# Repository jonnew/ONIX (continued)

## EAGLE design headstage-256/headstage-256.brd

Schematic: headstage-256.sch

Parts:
3V1: TPTP10R; TP10R
C1, C2: 0.1uF; 0201T; PARTNP CL03A104KA3NNNC
C3, C13, C14, C18, C19, C32, C51: 10nF; 0201T
C4, C12, C15, C17, C20, C43, C45, C47, C52, C57, C62, C63, C85, C89, C92, C93, C95, C100: 0.1uF; 0201T
C5, C16: 4.7uF; 0402T; PARTNO GRM155R61A475MEAAD
C6, C7, C8, C9, C24, C41, C42, C48, C60, C66, C71, C75, C79, C98: 0.1uF; 0201T; PARTNO C0603X5R1C104K030BC
C10, C11, C22, C23, C26, C27, C44: 0.1uF; 0201T; PARTNO CL03A104KA3NNNC
C21: 22uF; 0603T; PARTNO CL05A226MQ5QUNC
C25: 4.7uF; 0402T; PARTNO CL05A475MO5NUNC
C28: 0.1uF; 0201T; PARTNO C1005X7R1H104K050BB
C29: 47nF; 0201T; PARTNO C1005X7R1H473K050BB
C30: 1.5pF, NP0 +/-0.1pF; 0402T
C31: 1.0pF, NP0 +/- 0.1pF; 0402T
C33: 1nF; 0201T
C34: 33nF; 0201T
C35: 2.2nF; 0402T
C36: 4.7pF, NP0 +/-0.25pF; 0402T
C37, C40, C64, C69, C73: 1uF; 0402T; PARTNO CL05A105KO5NNNC
C38, C39, C49, C50: 22pF, NP0 2%; 0402T
C46: 6.8nF; 0201T; PARTNO CL03B103KP3NNNC
C53, C54, C77, C78, C86, C90, C96, C101: 4.7uF; 0402T
C55, C56: 22uF; 0603T
C58, C59, C80, C81: 10nF; 0201T; PARTNO GRM033R71E103KE14D
C61, C67, C72, C76, C82, C103: 1uF; 0201T; PARTNO CL03A105MP3ZSNH
C65, C70: 0.47uF; 0402T; PARTNO UMK105BJ224KV-F
C68: 10pF; 0201T
C74: 10uF; 0402T; PARTNO CL05A106MQ5NUNC
C83, C84, C88, C94, C99: 22nF; 0201T
C87, C91, C97, C102: 10uF; 0402T
D1: SESD0402X1UN-0020-090; 0402T-DFN
D2: SESD0402X1UN-0020-090; 0402P-DFN
D3: GDZ8V2BLP3-7; GDZ8V2BLP3
D4, D5, D9, D10, D11: VEMD1160X01; 0805PT
D6, D7: XZVGR155W; LED-0201T
D8: VSKY05401006; CLP1006-2L
GND: TPTP10R; TP10R
J1, J2: JP2E_COAX-ADAPTER-8X8MM-SIG-THRU; COAX-ADAPTER-8X8MM-SIG-THRU
J3: 142-0711-201; SMA_VERT
J4, J6: COAX_COAX-ADAPTER-8X8MM-THRU; COAX-ADAPTER-8X8MM-THRU
J5: MMCX-J-P-H-ST-SM1; MMCX-SMT-VERT
J7, J8: JP2E_COAX-ADAPTER-8X8MM-GND-THRU; COAX-ADAPTER-8X8MM-GND-THRU
J9: COAX_COAX-ADAPTER-8X8MM-SMD; COAX-ADAPTER-8X8MM
J10: X_FL_R_SMT_1(02)
J11: PINHD-2X10+4_DF40-HEAD; DF40-20HEAD
J12: PINHD-2X5+4DF40-HEAD; DF40-10HEAD
J13: 5041940270; MICROLOCK-1X2-VERT
JA: DF40C(2.0)-70DS-0.4V(51); DF40-70REC
JB: DF40C(2.0)-70DS-0.4V(51); DF40-70REC
JC: DF40C(2.0)-70DS-0.4V(51); DF40-70REC
JD: DF40C(2.0)-70DS-0.4V(51); DF40-70REC
L1, L2, L7, L13, L15, L18, L19: BLM15PX601SN1D; 0402T; PARTNO BLM15PX601SN1D
L3: BLM18KG601SN1D; 0603T
L4: CIG21L4R7MNE; 0805T
L5: CBC3225T101MR; 1210T
L6: 3.9nH, 5%; 0402T
L8: 8.2nH, 5%; 0402T
L9: 2.7nH, 5%; 0402T
L10: MMZ0603S601HT000; 0201T
L11: TFM201610ALM-2R2MTAA, 2.2 uH; 0806T
L12, L14: MLZ2012M100WT000; 0805T
L16: TFM201610ALMA1R5MTAA, 1.5uH; 0806T
L17: BLM15PX121SN1D; 0402T; PARTNO BLM15PX601SN1D
R1, R2, R48: 9k, 0.1%; 0201T
R3, R4, R51: 1k, 0.1%; 0201T
R5, R6, R7, R8, R9, R10, R11, R12, R13, R14, R19, R20, R21, R22, R23, R24, R25, R26, R27, R28, R29, R30: 10k, 0.1%; 0201T
R15, R17, R62, R65, R66, R69, R71, R73, R79, R95, R96, R97: 100; 0201T
R16, R18: 2.86k; 0201T
R31, R32, R58, R59: 1k; 0201T
R33: 49.9; 0201T
R34, R35, R46, R47: 590; 0201T
R36, R37, R38, R39, R40, R42, R45, R52, R53, R54, R55, R57, R82, R87, R88, R89, R91: 10k; 0201T
R41: 100k; 0201T
R43, R74, R85: 1M; 0201T
R44: 22K; 0201T
R49, R75: 0; 0201T
R50, R56, R76, R77: 4.7k; 0201T
R60, R61: 2M; 0201T
R63: 240k; 0201T
R64: 200k; 0201T
R67, R68, R93, R94: 0; 0402
R70, R80, R86, R90, R92, R98: 15k; 0201T
R72: 0 (DNP); 0201T
R78: 90.9k; 0201T
R81: 83.3k; 0201T
R83, R84: 2k; 0201T
TCK: TPTP10R; TP10R
TDI: TPTP10R; TP10R
TDO: TPTP10R; TP10R
TMS: TPTP10R; TP10R
TP1, TP2, TP3, TP4, TP5, TP6, TP7, TP8, TP9, TP10, TP12, TP27, TP33, TP35, TP36: TP_0.7MM; TESTPOINT_0.7MM
TP11, TP13, TP14, TP15: TPTP07R; TP07R
TP16, TP17, TP18, TP19, TP20, TP21, TP22, TP23, TP24, TP25, TP26, TP28, TP29, TP30, TP31, TP32, TP34: TPTP13R; TP13R
U1, U2: ADA4062-4ACPZ-R7; CP_16_27-L
U3, U4: AD5681RBCPZ-1RL7; CP_8_10-L
U5, U6: DG509B; MQFN16-1.8X2.6
U7: DS90UB913A_WQFN; WQFN32-5X5
U8: NRF24L01QFN; QFN20-4X4MM_NO-PAD
U9, U10: CAT4016_QFN; QFN24-4X4; PARTNO CAT4016HV6-GT2
U11, U12: TPL0501_UQFN; UQFN; PARTNO TPL0501-100RSER
U13: MICROSD_473093751; MICRO-SD-473093751
U14: 10M08SAM15317G; MBGA153-8X8
U15: Si8487DB; MICROFOOT-1.6X1.6MM
U16: MAX17048_WLP; WLP8-1.7X0.9
U17: BNO055; LGA-28-3.8X5.2
U18: ASCO-50.000MHZ-EK-T3; ASCO
U19: TPS61202; PWSON-N10+4-3X3
U20, U21, U28, U29: RHD2064_BGA; BGA104_0.5MM
U22, U23, U25, U27, U31, U32: TS4231; WLCSP3X3
U24: LT3463; DFN103X3
U26: TLV70733; X2SON
U30: MIC23150; TDFN_2X2MM
U33: TPS8268180; MICROSIP9-3X2.3
VCOAX: TPTP10R; TP10R
Y1: FW1600008; FW2X1.6MM
Y2: ECS-.327-12.5-1210-TR; ECX-1210

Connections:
!IMU_BL: R55.2, TP11.TP, U17.4 (!BOOT_LOAD)
!IMU_RESET: R57.1, U14.P4 (DIFFIO_RX_B4N/P4), U17.11 (!RESET)
!LIPO_ALRT: R50.1, U14.E7 (DIFFIO_RX_T22N/CRC_ERROR/E7), U16.B4 (!ALRT)
+1V8: C12.1, C13.1, C14.1, C15.1, C16.1, L1.1, L2.1, R38.1, U7.11 (VDDT), U7.28 (VDDD), U33.A1 (VOUT), U33.A2 (VOUT)
+3V3: 3V1.TP, C7.1, C9.1, C17.1, C18.1, C41.1, C42.1, C43.1, C45.1, C46.1, C47.1, C51.1, C60.1, C66.1, C71.1, C75.1, C77.1, C79.1, C98.1, C99.1, C100.1, C101.1, C102.1, J11.17, J11.18, J12.7, J12.8, L7.2, L16.1, L17.1, L18.1, L19.1, R36.1, R37.1, R42.1, R45.2, R50.2, R52.1, R53.1, R54.1, R55.1, R57.2, R72.2, R76.2, R77.2, R83.1, R84.1, R87.1, R88.1, R89.1, TP6.1, U3.2 (VLOGIC), U4.2 (VLOGIC), U7.25 (VDDIO), U11.7 (VDD), U12.7 (VDD), U13.VDD (VCC), U14.G8 (VCC_ONE/J8,H9,H7,G8), U14.H7 (VCC_ONE/J8,H9,H7,G8), U14.H9 (VCC_ONE/J8,H9,H7,G8), U14.J8 (VCC_ONE/J8,H9,H7,G8), U17.3 (VDD), U17.28 (VDDIO), U18.1 (EN), U18.4 (VCC), U22.C3 (DVDD), U23.C3 (DVDD), U25.C3 (DVDD), U27.C3 (DVDD), U30.4 (SNS), U31.C3 (DVDD), U32.C3 (DVDD)
+3V3_AN: C74.1, L15.1, R75.1
+15V0: C1.1, C2.1, C22.1, C23.1, C65.1, R74.2, U1.3 (V+), U2.3 (V+), U5.12 (V+), U6.12 (V+), U24.1 (VOUT1)
-15V0: C10.1, C11.1, C26.1, C27.1, C68.2, C70.1, D8.A, R85.1, U1.10 (V-), U1.PAD (V-), U2.10 (V-), U2.PAD (V-), U5.1 (V-), U6.1 (V-)
A/D_IN1: J11.5, U14.D4 (ANAIN1/D4)
A/D_VREF: J11.6, U14.F4 (ADC_VREF/F4)
ADAPT_SIG: D1.C, D2.C, J1.SIG (1), J2.SIG (1), J3.SIG (1), J4.SIG (1), J5.SIG (1), J6.SIG (1)
AGND: C58.2, C59.2, C62.1, C63.1, C80.2, C81.2, C92.1, C93.1, JA.70, JB.70, JC.35, JC.70, JD.35, JD.70, L13.2, R67.1, R68.1, R93.1, R94.1, TP23.TP, TP24.TP, TP25.TP, TP26.TP, U20.M2 (VESD), U20.M17 (GND), U20.N1 (GND), U20.N6 (GND), U21.M2 (VESD), U21.M17 (GND), U21.N1 (GND), U21.N6 (GND), U28.M2 (VESD), U28.M17 (GND), U28.N1 (GND), U28.N6 (GND), U29.M2 (VESD), U29.M17 (GND), U29.N1 (GND), U29.N6 (GND)
ANT: C30.2, C31.2, J10.P$1 (1)
AUXIN1_A: JD.34, TP16.TP, U20.N3 (AUXIN1)
AUXIN1_B: JC.34, TP28.TP, U28.N3 (AUXIN1)
AUXIN1_C: JC.69, TP18.TP, U21.N3 (AUXIN1)
AUXIN1_D: JD.69, TP30.TP, U29.N3 (AUXIN1)
AUXIN2_A: JD.36, TP17.TP, U20.N4 (AUXIN2)
AUXIN2_B: JC.36, TP29.TP, U28.N4 (AUXIN2)
AUXIN2_C: TP19.TP, U21.N4 (AUXIN2)
AUXIN2_D: TP31.TP, U29.N4 (AUXIN2)
AUXIN3_C: TP20.TP, U21.N5 (AUXIN3)
AUXIN3_D: TP32.TP, U29.N5 (AUXIN3)
CONFIG_SEL: R91.1, U14.D8 (CONFIG_SEL/D8)
CONF_DONE: R89.2, U14.E6 (DIFFIO_RX_T24N/CONF_DONE/E6)
DAC_A_CS: U3.5 (!SYNC), U14.G2 (VREFB1N0/G2)
DAC_B_CS: U4.5 (!SYNC), U14.J11 (DIFFIO_RX_R10N/J11)
DIN0: U7.19 (DIN0), U14.B11 (DIFFIO_RX_T19N/B11)
DIN1: U7.20 (DIN1), U14.B12 (DIFFIO_RX_T19P/B12)
DIN2: U7.21 (DIN2), U14.D11 (DIFFIO_RX_T14P/D11)
DIN3: U7.22 (DIN3), U14.A13 (VREFB8N0/A13)
DIN4: U7.23 (DIN4), U14.B13 (DIFFIO_RX_T17P/B13)
DIN5: U7.24 (DIN5), U14.A14 (DIFFIO_RX_T17N/A14)
DIN6: U7.26 (DIN6), U14.B14 (DIFFIO_RX_T15N/B14)
DIN7: U7.27 (DIN7), U14.B15 (DIFFIO_RX_T15P/B15)
DIN8: U7.29 (DIN8), U14.A9 (DIFFIO_RX_T21P/A9)
DIN9: U7.30 (DIN9), U14.A7 (DIFFIO_RX_T23P/A7)
DIN10: U7.31 (DIN10), U14.B8 (DIFFIO_RX_T16N/DEV_CLRN/B8)
DIN11: U7.32 (DIN11), U14.B7 (DIFFIO_RX_T20P/B7)
DOUT_N: C29.2, U7.12 (DOUT-)
DOUT_P: C28.2, U7.13 (DOUT+)
E0A: JA.2, U20.K2 (IN0)
E0B: JB.2, U28.K2 (IN0)
E0C: JC.2, U21.K2 (IN0)
E0D: JD.2, U29.K2 (IN0)
E1A: JA.68, U20.J1 (IN1)
E1B: JB.68, U28.J1 (IN1)
E1C: JC.68, U21.J1 (IN1)
E1D: JD.68, U29.J1 (IN1)
E2A: JA.3, U20.J2 (IN2)
E2B: JB.3, U28.J2 (IN2)
E2C: JC.3, U21.J2 (IN2)
E2D: JD.3, U29.J2 (IN2)
E3A: JA.67, U20.H1 (IN3)
E3B: JB.67, U28.H1 (IN3)
E3C: JC.67, U21.H1 (IN3)
E3D: JD.67, U29.H1 (IN3)
E4A: JA.4, U20.H2 (IN4)
E4B: JB.4, U28.H2 (IN4)
E4C: JC.4, U21.H2 (IN4)
E4D: JD.4, U29.H2 (IN4)
E5A: JA.66, U20.G1 (IN5)
E5B: JB.66, U28.G1 (IN5)
E5C: JC.66, U21.G1 (IN5)
E5D: JD.66, U29.G1 (IN5)
E6A: JA.5, U20.G2 (IN6)
E6B: JB.5, U28.G2 (IN6)
E6C: JC.5, U21.G2 (IN6)
E6D: JD.5, U29.G2 (IN6)
E7A: JA.65, U20.F1 (IN7)
E7B: JB.65, U28.F1 (IN7)
E7C: JC.65, U21.F1 (IN7)
E7D: JD.65, U29.F1 (IN7)
E8A: JA.6, U20.F2 (IN8)
E8B: JB.6, U28.F2 (IN8)
E8C: JC.6, U21.F2 (IN8)
E8D: JD.6, U29.F2 (IN8)
E9A: JA.64, U20.E1 (IN9)
E9B: JB.64, U28.E1 (IN9)
E9C: JC.64, U21.E1 (IN9)
E9D: JD.64, U29.E1 (IN9)
E10A: JA.7, U20.E2 (IN10)
E10B: JB.7, U28.E2 (IN10)
E10C: JC.7, U21.E2 (IN10)
E10D: JD.7, U29.E2 (IN10)
E11A: JA.63, U20.D1 (IN11)
E11B: JB.63, U28.D1 (IN11)
E11C: JC.63, U21.D1 (IN11)
E11D: JD.63, U29.D1 (IN11)
E12A: JA.8, U20.D2 (IN12)
E12B: JB.8, U28.D2 (IN12)
E12C: JC.8, U21.D2 (IN12)
E12D: JD.8, U29.D2 (IN12)
E13A: JA.62, U20.C1 (IN13)
E13B: JB.62, U28.C1 (IN13)
E13C: JC.62, U21.C1 (IN13)
E13D: JD.62, U29.C1 (IN13)
E14A: JA.9, U20.C2 (IN14)
E14B: JB.9, U28.C2 (IN14)
E14C: JC.9, U21.C2 (IN14)
E14D: JD.9, U29.C2 (IN14)
E15A: JA.61, U20.B1 (IN15)
E15B: JB.61, U28.B1 (IN15)
E15C: JC.61, U21.B1 (IN15)
E15D: JD.61, U29.B1 (IN15)
E16A: JA.10, U20.A1 (IN16)
E16B: JB.10, U28.A1 (IN16)
E16C: JC.10, U21.A1 (IN16)
E16D: JD.10, U29.A1 (IN16)
E17A: JA.60, U20.B2 (IN17)
E17B: JB.60, U28.B2 (IN17)
E17C: JC.60, U21.B2 (IN17)
E17D: JD.60, U29.B2 (IN17)
E18A: JA.11, U20.A2 (IN18)
E18B: JB.11, U28.A2 (IN18)
E18C: JC.11, U21.A2 (IN18)
E18D: JD.11, U29.A2 (IN18)
E19A: JA.59, U20.B3 (IN19)
E19B: JB.59, U28.B3 (IN19)
E19C: JC.59, U21.B3 (IN19)
E19D: JD.59, U29.B3 (IN19)
E20A: JA.12, U20.A3 (IN20)
E20B: JB.12, U28.A3 (IN20)
E20C: JC.12, U21.A3 (IN20)
E20D: JD.12, U29.A3 (IN20)
E21A: JA.58, U20.B4 (IN21)
E21B: JB.58, U28.B4 (IN21)
E21C: JC.58, U21.B4 (IN21)
E21D: JD.58, U29.B4 (IN21)
E22A: JA.13, U20.A4 (IN22)
E22B: JB.13, U28.A4 (IN22)
E22C: JC.13, U21.A4 (IN22)
E22D: JD.13, U29.A4 (IN22)
E23A: JA.57, U20.B5 (IN23)
E23B: JB.57, U28.B5 (IN23)
E23C: JC.57, U21.B5 (IN23)
E23D: JD.57, U29.B5 (IN23)
E24A: JA.14, U20.A5 (IN24)
E24B: JB.14, U28.A5 (IN24)
E24C: JC.14, U21.A5 (IN24)
E24D: JD.14, U29.A5 (IN24)
E25A: JA.56, U20.B6 (IN25)
E25B: JB.56, U28.B6 (IN25)
E25C: JC.56, U21.B6 (IN25)
E25D: JD.56, U29.B6 (IN25)
E26A: JA.15, U20.A6 (IN26)
E26B: JB.15, U28.A6 (IN26)
E26C: JC.15, U21.A6 (IN26)
E26D: JD.15, U29.A6 (IN26)
E27A: JA.55, U20.B7 (IN27)
E27B: JB.55, U28.B7 (IN27)
E27C: JC.55, U21.B7 (IN27)
E27D: JD.55, U29.B7 (IN27)
E28A: JA.16, U20.A7 (IN28)
E28B: JB.16, U28.A7 (IN28)
E28C: JC.16, U21.A7 (IN28)
E28D: JD.16, U29.A7 (IN28)
E29A: JA.54, U20.B8 (IN29)
E29B: JB.54, U28.B8 (IN29)
E29C: JC.54, U21.B8 (IN29)
E29D: JD.54, U29.B8 (IN29)
E30A: JA.17, U20.A8 (IN30)
E30B: JB.17, U28.A8 (IN30)
E30C: JC.17, U21.A8 (IN30)
E30D: JD.17, U29.A8 (IN30)
E31A: JA.53, U20.B9 (IN31)
E31B: JB.53, U28.B9 (IN31)
E31C: JC.53, U21.B9 (IN31)
E31D: JD.53, U29.B9 (IN31)
E32A: JA.18, U20.A9 (IN32)
E32B: JB.18, U28.A9 (IN32)
E32C: JC.18, U21.A9 (IN32)
E32D: JD.18, U29.A9 (IN32)
E33A: JA.52, U20.A10 (IN33)
E33B: JB.52, U28.A10 (IN33)
E33C: JC.52, U21.A10 (IN33)
E33D: JD.52, U29.A10 (IN33)
E34A: JA.19, U20.B10 (IN34)
E34B: JB.19, U28.B10 (IN34)
E34C: JC.19, U21.B10 (IN34)
E34D: JD.19, U29.B10 (IN34)
E35A: JA.51, U20.A11 (IN35)
E35B: JB.51, U28.A11 (IN35)
E35C: JC.51, U21.A11 (IN35)
E35D: JD.51, U29.A11 (IN35)
E36A: JA.20, U20.B11 (IN36)
E36B: JB.20, U28.B11 (IN36)
E36C: JC.20, U21.B11 (IN36)
E36D: JD.20, U29.B11 (IN36)
E37A: JA.50, U20.A12 (IN37)
E37B: JB.50, U28.A12 (IN37)
E37C: JC.50, U21.A12 (IN37)
E37D: JD.50, U29.A12 (IN37)
E38A: JA.21, U20.B12 (IN38)
E38B: JB.21, U28.B12 (IN38)
E38C: JC.21, U21.B12 (IN38)
E38D: JD.21, U29.B12 (IN38)
E39A: JA.49, U20.A13 (IN39)
E39B: JB.49, U28.A13 (IN39)
E39C: JC.49, U21.A13 (IN39)
E39D: JD.49, U29.A13 (IN39)
E40A: JA.22, U20.B13 (IN40)
E40B: JB.22, U28.B13 (IN40)
E40C: JC.22, U21.B13 (IN40)
E40D: JD.22, U29.B13 (IN40)
E41A: JA.48, U20.A14 (IN41)
E41B: JB.48, U28.A14 (IN41)
E41C: JC.48, U21.A14 (IN41)
E41D: JD.48, U29.A14 (IN41)
E42A: JA.23, U20.B14 (IN42)
E42B: JB.23, U28.B14 (IN42)
E42C: JC.23, U21.B14 (IN42)
E42D: JD.23, U29.B14 (IN42)
E43A: JA.47, U20.A15 (IN43)
E43B: JB.47, U28.A15 (IN43)
E43C: JC.47, U21.A15 (IN43)
E43D: JD.47, U29.A15 (IN43)
E44A: JA.24, U20.B15 (IN44)
E44B: JB.24, U28.B15 (IN44)
E44C: JC.24, U21.B15 (IN44)
E44D: JD.24, U29.B15 (IN44)
E45A: JA.46, U20.A16 (IN45)
E45B: JB.46, U28.A16 (IN45)
E45C: JC.46, U21.A16 (IN45)
E45D: JD.46, U29.A16 (IN45)
E46A: JA.25, U20.B16 (IN46)
E46B: JB.25, U28.B16 (IN46)
E46C: JC.25, U21.B16 (IN46)
E46D: JD.25, U29.B16 (IN46)
E47A: JA.45, U20.A17 (IN47)
E47B: JB.45, U28.A17 (IN47)
E47C: JC.45, U21.A17 (IN47)
E47D: JD.45, U29.A17 (IN47)
E48A: JA.26, U20.B17 (IN48)
E48B: JB.26, U28.B17 (IN48)
E48C: JC.26, U21.B17 (IN48)
E48D: JD.26, U29.B17 (IN48)
E49A: JA.44, U20.C16 (IN49)
E49B: JB.44, U28.C16 (IN49)
E49C: JC.44, U21.C16 (IN49)
E49D: JD.44, U29.C16 (IN49)
E50A: JA.27, U20.C17 (IN50)
E50B: JB.27, U28.C17 (IN50)
E50C: JC.27, U21.C17 (IN50)
E50D: JD.27, U29.C17 (IN50)
E51A: JA.43, U20.D16 (IN51)
E51B: JB.43, U28.D16 (IN51)
E51C: JC.43, U21.D16 (IN51)
E51D: JD.43, U29.D16 (IN51)
E52A: JA.28, U20.D17 (IN52)
E52B: JB.28, U28.D17 (IN52)
E52C: JC.28, U21.D17 (IN52)
E52D: JD.28, U29.D17 (IN52)
E53A: JA.42, U20.E16 (IN53)
E53B: JB.42, U28.E16 (IN53)
E53C: JC.42, U21.E16 (IN53)
E53D: JD.42, U29.E16 (IN53)
E54A: JA.29, U20.E17 (IN54)
E54B: JB.29, U28.E17 (IN54)
E54C: JC.29, U21.E17 (IN54)
E54D: JD.29, U29.E17 (IN54)
E55A: JA.41, U20.F16 (IN55)
E55B: JB.41, U28.F16 (IN55)
E55C: JC.41, U21.F16 (IN55)
E55D: JD.41, U29.F16 (IN55)
E56A: JA.30, U20.F17 (IN56)
E56B: JB.30, U28.F17 (IN56)
E56C: JC.30, U21.F17 (IN56)
E56D: JD.30, U29.F17 (IN56)
E57A: JA.40, U20.G16 (IN57)
E57B: JB.40, U28.G16 (IN57)
E57C: JC.40, U21.G16 (IN57)
E57D: JD.40, U29.G16 (IN57)
E58A: JA.31, U20.G17 (IN58)
E58B: JB.31, U28.G17 (IN58)
E58C: JC.31, U21.G17 (IN58)
E58D: JD.31, U29.G17 (IN58)
E59A: JA.39, U20.H16 (IN59)
E59B: JB.39, U28.H16 (IN59)
E59C: JC.39, U21.H16 (IN59)
E59D: JD.39, U29.H16 (IN59)
E60A: JA.32, U20.H17 (IN60)
E60B: JB.32, U28.H17 (IN60)
E60C: JC.32, U21.H17 (IN60)
E60D: JD.32, U29.H17 (IN60)
E61A: JA.38, U20.J16 (IN61)
E61B: JB.38, U28.J16 (IN61)
E61C: JC.38, U21.J16 (IN61)
E61D: JD.38, U29.J16 (IN61)
E62A: JA.33, U20.J17 (IN62)
E62B: JB.33, U28.J17 (IN62)
E62C: JC.33, U21.J17 (IN62)
E62D: JD.33, U29.J17 (IN62)
E63A: JA.37, U20.K16 (IN63)
E63B: JB.37, U28.K16 (IN63)
E63C: JC.37, U21.K16 (IN63)
E63D: JD.37, U29.K16 (IN63)
ESTIM_POW_EN: R82.1, U14.K4 (DIFFIO_RX_L20P/CLK1P/K4), U24.8 (!SHDN2), U24.9 (!SHDN1)
EXP1: J11.13, U14.D2 (DIFFIO_RX_L1N/ADCIN1/D2)
EXP2: J11.2, U14.C2 (DIFFIO_RX_L1P/ADCIN2/C2)
EXP3: J11.8, U14.F5 (DIFFIO_RX_L3N/ADCIN3/F5)
EXP4: J11.10, U14.G5 (DIFFIO_RX_L3P/ADCIN4/G5)
EXP5/VMEAS: J11.1, R49.1, U14.C1 (DIFFIO_RX_L5N/ADCIN5/C1)
EXP6: J11.14, U14.B1 (DIFFIO_RX_L5P/ADCIN6/B1)
EXP7: J11.3, U14.E1 (DIFFIO_RX_L7N/ADCIN7/E1)
EXP8: J11.15, U14.E2 (DIFFIO_RX_L7P/ADCIN8/E2)
EXP9: J12.5, U14.R7 (DIFFIO_RX_B6N/R7)
EXP10: J12.4, U14.P8 (DIFFIO_RX_B6P/P8)
EXP11: J12.2, U14.M8 (DIFFIO_TX_RX_B9N/M8)
EXP12: J12.1, U14.R11 (VREFB3N0/R11)
EXP13: J12.3, U14.N8 (DIFFIO_TX_RX_B9P/N8)
EXP14: J12.6, U14.P12
FB1: R61.1, R64.2, U19.10 (FB)
GND: C1.2, C2.2, C3.2, C4.2, C5.2, C6.2, C7.2, C8.2, C9.2, C10.2, C11.2, C12.2, C13.2, C14.2, C15.2, C16.2, C17.2, C18.2, C19.2, C20.2, C21.2, C22.2, C23.2, C24.2, C25.2, C26.2, C27.2, C31.1, C32.2, C33.2, C34.2, C35.2, C36.2, C37.2, C38.2, C39.2, C40.2, C41.2, C42.2, C43.2, C44.2, C45.2, C46.2, C47.2, C48.1, C49.2, C50.2, C51.2, C53.2, C54.2, C55.2, C56.2, C57.2, C60.2, C61.2, C64.2, C65.2, C66.2, C67.2, C70.2, C71.2, C72.2, C73.2, C74.2, C75.2, C76.2, C77.2, C78.2, C79.2, C82.2, C83.2, C84.2, C85.2, C86.2, C87.2, C88.2, C89.2, C90.2, C91.2, C94.2, C95.2, C96.2, C97.2, C98.2, C99.2, C100.2, C101.2, C102.2, C103.2, GND.TP, J9.GND1 (2), J9.GND2 (2), J9.GND3 (2), J9.GND4 (2), J10.P$2 (2), J10.P$3 (2), J10.P$4 (2), J11.4, J11.7, J11.9, J11.11, J11.12, J11.16, J11.M1, J11.M2, J11.M3, J11.M4, J12.9, J12.10, J12.M1, J12.M2, J12.M3, J12.M4, J13.2, J13.M2 (4), L10.1, L13.1, R29.1, R30.1, R33.1, R34.1, R35.1, R39.2, R40.2, R41.2, R44.2, R51.1, R56.1, R58.1, R59.2, R63.1, R64.1, R70.1, R78.1, R80.1, R82.2, R86.1, R90.1, R91.2, R92.1, R98.1, TP7.1, TP8.1, TP9.1, TP12.1, U3.3 (GND), U3.PAD (GND), U4.3 (GND), U4.PAD (GND), U5.2 (X0), U5.13 (GND), U5.14 (B), U6.2 (X0), U6.3 (X1), U6.13 (GND), U6.14 (B), U7.6 (ID), U7.7 (RES), U7.PAD (GND), U8.8 (VSS), U8.14 (VSS), U8.17 (VSS), U8.20 (VSS), U9.1 (GND), U9.PAD (GND), U10.1 (GND), U10.PAD (GND), U11.4 (GND), U11.8 (LA), U12.4 (GND), U12.8 (LA), U13.G1 (GND), U13.G2 (GND), U13.G3 (POL), U13.VSS (GND), U14.A1 (GND), U14.A15 (GND), U14.B2 (GND), U14.D5 (GND), U14.D9 (GND), U14.E5 (GND), U14.E12 (GND), U14.G4 (GND), U14.G9 (GND), U14.H8 (GND), U14.H14 (GND), U14.J7 (GND), U14.L12 (GND), U14.M2 (GND), U14.M6 (GND), U14.M10 (GND), U14.R1 (GND), U14.R15 (GND), U16.A1 (CTG), U16.A4 (GND), U17.2 (GND), U17.5 (PS1), U17.6 (PS0), U17.15 (GNDIO), U17.16 (GNDIO), U17.17 (COM3/ADDR), U17.18 (COM2), U17.25 (GNDIO), U18.2 (GND), U19.4 (PGND), U19.9 (GND), U19.PAD (PGND), U19.PAD1 (PGND), U19.PAD2 (PGND), U19.PAD3 (PGND), U19.PAD4 (PGND), U22.B2 (AVSS), U22.B3 (AVSS2), U23.B2 (AVSS), U23.B3 (AVSS2), U24.PAD (GND), U25.B2 (AVSS), U25.B3 (AVSS2), U26.2 (GND), U26.PAD (GND), U27.B2 (AVSS), U27.B3 (AVSS2), U30.5 (AGND), U30.8 (PGND), U31.B2 (AVSS), U31.B3 (AVSS2), U32.B2 (AVSS), U32.B3 (AVSS2), U33.C1 (GND), U33.C2 (GND), U33.C3 (GND), Y1.2 (CAN), Y1.4 (CAN)
GND1: D1.A, D2.A, J1.GND1 (2), J1.GND2 (2), J1.GND3 (2), J1.GND4 (2), J2.GND1 (2), J2.GND2 (2), J2.GND3 (2), J2.GND4 (2), J3.G1 (2), J3.G2 (2), J3.G3 (2), J3.G4 (2), J4.GND1 (2), J4.GND2 (2), J4.GND3 (2), J4.GND5 (2), J4.GND6 (2), J4.GND7 (2), J4.GND9 (2), J4.GND12 (2), J5.GND@1 (2), J5.GND@2 (2), J5.GND@3 (2), J5.GND@4 (2), J6.GND1 (2), J6.GND2 (2), J6.GND3 (2), J6.GND5 (2), J6.GND6 (2), J6.GND7 (2), J6.GND9 (2), J6.GND12 (2), J7.GND1 (1), J7.GND2 (1), J7.GND3 (2), J7.GND4 (2), J8.GND1 (1), J8.GND2 (1), J8.GND3 (2), J8.GND4 (2)
HSYNC: U7.1 (HSYNC), U14.A5 (DIFFIO_RX_T23N/A5)
IMEAS_A: R19.1, R29.2, U20.N5 (AUXIN3)
IMEAS_B: R20.1, R30.2, U28.N5 (AUXIN3)
IMU_BL_IND: TP13.TP, U17.10 (BL_IND)
IMU_INT: U14.R5 (DIFFIO_RX_B4P/R5), U17.14 (INT)
INTAN_EN: U14.K2 (DIFFIO_RX_L16P/K2), U26.3 (EN)
INTAN_VDD: C62.2, C63.2, C92.2, C93.2, R72.1, R75.2, U20.M15 (VDD), U20.M16 (LVDS_EN), U20.N2 (VDD), U20.N15 (VDD), U21.M15 (VDD), U21.M16 (LVDS_EN), U21.N2 (VDD), U21.N15 (VDD), U28.M15 (VDD), U28.M16 (LVDS_EN), U28.N2 (VDD), U28.N15 (VDD), U29.M15 (VDD), U29.M16 (LVDS_EN), U29.N2 (VDD), U29.N15 (VDD)
ISTIM_A: JA.69, U5.6 (X), U5.10 (Y1)
ISTIM_A_PRE: R15.1, U1.9 (+IN), U5.7 (Y)
ISTIM_B: JB.69, U6.6 (X), U6.10 (Y1)
ISTIM_B_PRE: R17.1, U2.9 (+IN), U6.7 (Y)
JTAGEN: R52.2, U14.G7 (JTAGEN/G7)
LED_BLANK: U9.21 (BLANK), U10.21 (BLANK), U14.G15 (DIFFIO_RX_R18N/G15)
LED_CAT0_A: JA.34, U9.5 (LED1), U9.6 (LED2), U9.7 (LED3), U9.8 (LED4), U9.9 (LED5), U9.10 (LED6), U9.11 (LED7), U9.12 (LED8)
LED_CAT0_B: JB.34, U10.5 (LED1), U10.6 (LED2), U10.7 (LED3), U10.8 (LED4), U10.9 (LED5), U10.10 (LED6), U10.11 (LED7), U10.12 (LED8)
LED_CAT1_A: JA.35, U9.13 (LED9), U9.14 (LED10), U9.15 (LED11), U9.16 (LED12), U9.17 (LED13), U9.18 (LED14), U9.19 (LED15), U9.20 (LED16)
LED_CAT1_B: JB.35, U10.13 (LED9), U10.14 (LED10), U10.15 (LED11), U10.16 (LED12), U10.17 (LED13), U10.18 (LED14), U10.19 (LED15), U10.20 (LED16)
LED_CLK: U9.3 (CLK), U10.3 (CLK), U14.E11 (DIFFIO_RX_R33P/E11)
LED_LATCH: U9.4 (LATCH), U10.4 (LATCH), U14.E14
LED_SIN: U10.2 (SIN), U14.D12 (DIFFIO_RX_R33N/D12)
LH_DATA1: TP15.TP, U14.C14 (DIFFIO_RX_R28N/C14), U22.C1 (D/CFGDATA)
LH_DATA2: U14.P2 (DIFFIO_RX_L27P/PLL_L_CLKOUTP/P2), U23.C1 (D/CFGDATA)
LH_DATA3: U14.L15 (VREFB5N0/L15), U25.C1 (D/CFGDATA)
LH_DATA4: U14.J15 (DIFFIO_RX_R18P/J15), U27.C1 (D/CFGDATA)
LH_DATA5: U14.J2 (DIFFIO_RX_L14P/J2), U31.C1 (D/CFGDATA)
LH_DATA6: U14.F11 (DIFFIO_RX_R27P/F11), U32.C1 (D/CFGDATA)
LH_ENV1: TP14.TP, U14.C15 (DIFFIO_RX_R28P/C15), U22.C2 (E/CFGCLK)
LH_ENV2: U14.R2, U23.C2 (E/CFGCLK)
LH_ENV3: U14.M14, U25.C2 (E/CFGCLK)
LH_ENV4: U14.J14 (DIFFIO_RX_R11N/J14), U27.C2 (E/CFGCLK)
LH_ENV5: U14.J4 (DIFFIO_RX_L18N/CLK0N/J4), U31.C2 (E/CFGCLK)
LH_ENV6: U14.F12 (DIFFIO_RX_R27N/F12), U32.C2 (E/CFGCLK)
LIPO_QSTRT: R56.2, U14.A2 (DIFFIO_RX_T26P/A2), U16.B3 (QSTRT)
MAIN_SUPPLY: C24.1, C25.1, L3.1, L5.2, R32.2
MIDFILT: L4.2, L5.1, R31.2, R32.1
MOSI: U3.6 (DIN), U4.6 (DIN), U11.2 (DIN), U12.2 (DIN), U14.J12 (DIFFIO_RX_R14P/CLK2P/J12)
unnamed: C58.1, U20.N17 (ADC_REF)
unnamed: C80.1, U28.N17 (ADC_REF)
unnamed: D9.C, U25.A3 (IIN-)
unnamed: C59.1, U21.N17 (ADC_REF)
unnamed: D9.A, U25.A2 (IIN+)
unnamed: C81.1, U29.N17 (ADC_REF)
unnamed: R86.2, U25.B1 (RBIAS)
unnamed: C72.1, U25.A1 (AVDD)
unnamed: D3.A, R58.2, U15.1 (G)
unnamed: C69.1, L14.1, U24.4 (SW2)
unnamed: L12.1, U24.2 (SW1)
unnamed: C69.2, D8.C, U24.5 (D2)
unnamed: D5.C, U23.A3 (IIN-)
unnamed: D5.A, U23.A2 (IIN+)
unnamed: C68.1, R81.1, R85.2, U24.6 (FB2)
unnamed: R81.2, U24.7 (VREF)
unnamed: C50.1, U17.26 (XOUT32), Y2.P$2 (2)
unnamed: J13.1, J13.M1 (3), TP10.1, U15.2 (D), U15.3 (D)
unnamed: R80.2, U23.B1 (RBIAS)
unnamed: C67.1, U23.A1 (AVDD)
unnamed: C49.1, U17.27 (XIN32), Y2.P$1 (1)
unnamed: U14.J5 (DIFFIO_RX_L18P/CLK0P/J5), U18.3 (OUT)
unnamed: TP21.TP, U20.N16 (AUXOUT)
unnamed: R74.1, R78.2, U24.10 (FB1)
unnamed: D4.C, U22.A3 (IIN-)
unnamed: D4.A, U22.A2 (IIN+)
unnamed: R70.2, U22.B1 (RBIAS)
unnamed: C61.1, U22.A1 (AVDD)
unnamed: L11.1, U19.3 (L)
unnamed: C57.1, U19.1 (VAUX)
unnamed: R36.2, U5.16 (EN)
unnamed: TP34.TP, U28.N16 (AUXOUT)
unnamed: D10.C, U27.A3 (IIN-)
unnamed: D10.A, U27.A2 (IIN+)
unnamed: R90.2, U27.B1 (RBIAS)
unnamed: C76.1, U27.A1 (AVDD)
unnamed: C38.1, R43.1, U8.9 (XC2), Y1.1
unnamed: C39.1, R43.2, U8.10 (XC1), Y1.3 (2)
unnamed: TP22.TP, U21.N16 (AUXOUT)
unnamed: R37.2, U6.16 (EN)
unnamed: R44.1, U8.16 (IREF)
unnamed: L6.1, L8.2, U8.13 (ANT2)
unnamed: R2.1, R6.2, U2.2 (+IN)
unnamed: R10.2, R22.1, U2.1 (-IN)
unnamed: C29.1, R33.2
unnamed: R42.2, U7.9 (PDB)
unnamed: R38.2, R41.1, U7.8 (MODE)
unnamed: C3.1, C4.1, C5.1, L1.2, U7.10 (VDDPLL)
unnamed: C19.1, C20.1, C21.1, L2.2, U7.14 (VDDCML)
unnamed: R2.2, R4.2, R17.2, U2.4 (+IN)
unnamed: R48.2, R49.2, R51.2
unnamed: R24.1, R27.2, U2.6 (OUT)
unnamed: R1.1, R5.2, U1.2 (+IN)
unnamed: R34.2, U5.11 (Y0)
unnamed: R46.2, U11.6 (WA)
unnamed: R46.1, U9.23 (RSET)
unnamed: R3.1, R21.2, U1.15 (OUT)
unnamed: R4.1, R22.2, U2.15 (OUT)
unnamed: R7.2, R21.1, U1.1 (-IN)
unnamed: R35.2, U6.11 (Y0)
unnamed: R47.2, U12.6 (WA)
unnamed: R47.1, U10.23 (RSET)
unnamed: L8.1, L9.2, U8.12 (ANT1)
unnamed: C30.1, L6.2
unnamed: C48.2, U17.9 (CAP)
unnamed: R1.2, R3.2, R15.2, U1.4 (+IN)
unnamed: U9.2 (SIN), U10.22 (SOUT)
unnamed: C34.1, U8.19 (DVDD)
unnamed: R23.1, R25.2, U1.6 (OUT)
unnamed: R16.1, R23.2, U1.5 (-IN)
unnamed: R13.1, R16.2, U1.8 (-IN)
unnamed: R8.2, R13.2, U1.7 (OUT)
unnamed: R9.1, R19.2, U1.14 (OUT)
unnamed: R8.1, R9.2, U1.12 (-IN)
unnamed: R25.1, R26.2, U1.11 (+IN)
unnamed: R18.1, R24.2, U2.5 (-IN)
unnamed: R14.1, R18.2, U2.8 (-IN)
unnamed: R11.2, R14.2, U2.7 (OUT)
unnamed: TP35.1, U32.A3 (IIN-)
unnamed: TP36.1, U32.A2 (IIN+)
unnamed: R98.2, U32.B1 (RBIAS)
unnamed: R12.1, R20.2, U2.14 (OUT)
unnamed: R11.1, R12.2, U2.12 (-IN)
unnamed: R27.1, R28.2, U2.11 (+IN)
unnamed: C103.1, U32.A1 (AVDD)
unnamed: D6.2 (A), R83.2
unnamed: D7.2 (A), R84.2
unnamed: L16.2, U30.1 (SW), U30.2 (SW)
unnamed: D11.C, TP27.1, U31.A3 (IIN-)
unnamed: D11.A, TP33.1, U31.A2 (IIN+)
unnamed: R92.2, U31.B1 (RBIAS)
unnamed: C82.1, U31.A1 (AVDD)
NCONFIG: R87.2, U14.E8 (NCONFIG/E8)
NRF_CS: U8.2 (CSN), U14.K12 (DIFFIO_RX_R7N/K12)
NRF_EN: U8.1 (CE), U14.K14 (DIFFIO_RX_R11P/K14)
NRF_IRQ: U8.6 (!IRQ), U14.J9 (DIFFIO_RX_R10P/J9)
NRF_MISO: U8.5 (MISO), U14.M12 (DIFFIO_RX_R1P/M12)
NRF_MOSI: U8.4 (MOSI), U14.N14 (DIFFIO_RX_R2N/N14)
NRF_SCLK: U8.3 (SCK), U14.N15 (DIFFIO_RX_R2P/N15)
NSTATUS: R88.2, U14.D6 (DIFFIO_RX_T24P/NSTATUS/D6)
OUT: L15.2, U26.1 (OUT)
PCLK: U7.3 (PCLK1), U14.C8 (DIFFIO_RX_T16P/C8)
POTA_CS: U11.3 (!CS), U14.H3 (DIFFIO_RX_L14N/H3)
POTB_CS: U12.3 (!CS), U14.E15 (VREFB6N0/E15)
REFGND: L10.2, U14.E4 (REFGND/E4)
REF_A: JA.1, R67.2, U20.M1 (REF_ELEC)
REF_B: JB.1, R93.2, U28.M1 (REF_ELEC)
REF_C: JC.1, R68.2, U21.M1 (REF_ELEC)
REF_D: JD.1, R94.2, U29.M1 (REF_ELEC)
RHD_CLK+_AC: R73.2, U14.L7 (DIFFIO_TX_RX_B3P/L7), U20.N10 (SCLK+), U21.N10 (SCLK+)
RHD_CLK+_BD: R96.2, U14.M9 (DIFFIO_TX_RX_B12P/M9), U28.N10 (SCLK+), U29.N10 (SCLK+)
RHD_CLK-_AC: R73.1, U14.L6 (DIFFIO_TX_RX_B3N/L6), U20.N9 (SCLK-), U21.N9 (SCLK-)
RHD_CLK-_BD: R96.1, U14.L9 (DIFFIO_TX_RX_B12N/L9), U28.N9 (SCLK-), U29.N9 (SCLK-)
RHD_CS+_AC: R69.2, U14.M5 (DIFFIO_TX_RX_B1P/M5), U20.N8 (!CS!+), U21.N8 (!CS!+)
RHD_CS+_BD: R95.2, U14.R13 (DIFFIO_TX_RX_B16P/R13), U28.N8 (!CS!+), U29.N8 (!CS!+)
RHD_CS-_AC: R69.1, U14.M4 (DIFFIO_TX_RX_B1N/M4), U20.N7 (!CS!-), U21.N7 (!CS!-)
RHD_CS-_BD: R95.1, U14.P14 (DIFFIO_TX_RX_B16N/P14), U28.N7 (!CS!-), U29.N7 (!CS!-)
RHD_MISO+_A: R62.2, U14.R3 (DIFFIO_RX_B2P/R3), U20.N14 (MISO+)
RHD_MISO+_B: R71.1, U14.P15 (DIFFIO_TX_RX_B10P/P15), U28.N14 (MISO+)
RHD_MISO+_C: R65.1, U14.M7 (DIFFIO_TX_RX_B7P/M7), U21.N14 (MISO+)
RHD_MISO+_D: R66.1, U14.R9 (DIFFIO_RX_B8P/R9), U29.N14 (MISO+)
RHD_MISO-_A: R62.1, U14.P3 (DIFFIO_RX_B2N/P3), U20.N13 (MISO-)
RHD_MISO-_B: R71.2, U14.R14 (DIFFIO_TX_RX_B10N/R14), U28.N13 (MISO-)
RHD_MISO-_C: R65.2, U14.L8 (DIFFIO_TX_RX_B7N/L8), U21.N13 (MISO-)
RHD_MISO-_D: R66.2, U14.P9 (DIFFIO_RX_B8N/P9), U29.N13 (MISO-)
RHD_MOSI+_AC: R79.2, U14.P7 (DIFFIO_TX_RX_B5P/P7), U20.N12 (MOSI+), U21.N12 (MOSI+)
RHD_MOSI+_BD: R97.2, U14.M11 (DIFFIO_TX_RX_B14P/M11), U28.N12 (MOSI+), U29.N12 (MOSI+)
RHD_MOSI-_AC: R79.1, U14.P6 (DIFFIO_TX_RX_B5N/P6), U20.N11 (MOSI-), U21.N11 (MOSI-)
RHD_MOSI-_BD: R97.1, U14.L10 (DIFFIO_TX_RX_B14N/L10), U28.N11 (MOSI-), U29.N11 (MOSI-)
SCL: R76.1, U14.K11 (DIFFIO_RX_R7P/K11), U16.B2 (SCL), U17.19 (COM1/SCL/RX)
SCLK: U3.4 (SCLK), U4.4 (SCLK), U11.5 (SCLK), U12.5 (SCLK), U14.H13 (DIFFIO_RX_R16N/CLK3N/H13)
SDA: R77.1, U14.L11 (DIFFIO_RX_R1N/L11), U16.B1 (SDA), U17.20 (COM0/SDA/TX)
SD_CS: U13.CD/DATA3 (DAT3/!CS), U14.L1 (DIFFIO_RX_L16N/L1)
SD_DAT2: U13.DAT2, U14.K5 (DIFFIO_RX_L20N/CLK1N/K5)
SD_DET: R45.1, U13.G4 (DET)
SD_IRQ: U13.DAT1 (DAT1/!IRQ), U14.P1 (VREFB2N0/P1)
SD_MISO: U13.DAT0 (DAT0/MISO), U14.N1 (DIFFIO_RX_L27N/PLL_L_CLKOUTN/N1)
SD_MOSI: U13.CMD (CMD/MOSI), U14.L4 (DIFFIO_RX_L22P/DPCLK1/L4)
SD_SCLK: U13.CLK (CLK/SLCK), U14.L5 (DIFFIO_RX_L22N/DPCLK0/L5)
SERDES_EN: U14.D7 (DIFFIO_RX_T22P/D7), U33.B2 (EN)
SERDES_GPIO0: TP1.1, U7.15 (GPIO0), U14.E9 (DIFFIO_RX_T18N/E9)
SERDES_GPIO1: TP2.1, U7.16 (GPIO1), U14.D10 (DIFFIO_RX_T14N/D10)
SERDES_GPIO2: TP3.1, U7.17 (GPIO2/CLKOUT), U14.E10 (DIFFIO_RX_T18P/DEV_OE/E10)
SERDES_GPIO3: TP4.1, U7.18 (GPO3/CLKIN), U14.A11 (DIFFIO_RX_T21N/A11)
SERDES_SCL: U7.4 (SCL), U14.B4
SERDES_SDA: U7.5 (SDA), U14.B6 (DIFFIO_RX_T20N/B6)
SIGOUT: C28.1, J9.SIG (1), L4.1, R31.1
STATUS_A: D7.1 (C), U14.G11 (DIFFIO_RX_R26P/DPCLK3/G11)
STATUS_B: D6.1 (C), U14.G12 (DIFFIO_RX_R26N/DPCLK2/G12)
STIM_NULL_A: R39.1, U5.15 (A), U14.H11 (DIFFIO_RX_R14N/CLK2N/H11)
STIM_NULL_B: R40.1, U6.15 (A), U14.H12 (DIFFIO_RX_R16P/CLK3P/H12)
TCK: R59.1, TCK.TP, U14.J1 (DIFFIO_RX_L11P/TCK/J1)
TDI: R54.2, TDI.TP, U14.H5 (DIFFIO_RX_L12N/TDI/H5)
TDO: TDO.TP, U14.H4 (DIFFIO_RX_L12P/TDO/H4)
TMS: R53.2, TMS.TP, U14.G1 (DIFFIO_RX_L11N/TMS/G1)
UVLO: C52.2, R60.1, R63.2, U19.7 (UVLO)
VCCA: C94.1, C95.1, C96.1, C97.1, L19.2, U14.B3 (VCCA3/B3), U14.D14 (VCCA2/D14), U14.N2 (VCCA1/N2), U14.P13 (VCCA4/P13)
VCCIO: C83.1, C84.1, C85.1, C86.1, C87.1, L17.2, U14.B5 (VCCIO8/B9,B5,B10), U14.B9 (VCCIO8/B9,B5,B10), U14.B10 (VCCIO8/B9,B5,B10), U14.F14 (VCCIO6/G14,F14), U14.G14 (VCCIO6/G14,F14), U14.H2 (VCCIO1B/H2), U14.L2 (VCCIO2/L2), U14.L14 (VCCIO5/L14), U14.P5 (VCCIO3/P5,P11,P10), U14.P10 (VCCIO3/P5,P11,P10), U14.P11 (VCCIO3/P5,P11,P10)
VCCIOA: C88.1, C89.1, C90.1, C91.1, L18.2, U14.F2 (VCCIO1A/F2)
VCOAX: C6.1, C8.1, C37.1, C40.1, C55.1, C56.1, C64.1, C73.1, C78.1, J11.19, J11.20, JA.36, JB.36, L3.2, L12.2, L14.2, R48.1, R61.2, TP5.1, U3.1 (AVDD), U4.1 (AVDD), U9.24 (VDD), U10.24 (VDD), U19.2 (VO), U24.3 (VIN), U26.4 (IN), U30.3 (EN), U30.6 (VIN), U30.7 (VIN), U33.A3 (VIN), U33.B1 (MODE), U33.B3 (VIN), VCOAX.TP
VDAC_A: R5.1, U3.8 (VOUT)
VDAC_B: R6.1, U4.8 (VOUT)
VDD_NRF: C32.1, C33.1, L7.1, U8.7 (VDD), U8.15 (VDD), U8.18 (VDD)
VDD_PA: C35.1, C36.1, L9.1, U8.11 (VDD_PA)
VREF_2V5_A: R7.1, R26.1, U3.7 (VREF)
VREF_2V5_B: R10.1, R28.1, U4.7 (VREF)
VSYNC: U7.2 (VSYNC), U14.A3 (DIFFIO_RX_T26N/A3)
V_LIPO: C44.1, C52.1, C53.1, C54.1, D3.C, L11.2, R60.2, U15.4 (S), U16.A2 (CELL), U16.A3 (VDD), U19.5 (VI), U19.6 (EN), U19.8 (PS)

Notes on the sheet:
NB: Core logic is LDOed from VCC_ONE
NB: Supply voltage for PLL regulator and ADC block (analog). Also determines ADC max voltage. Use 3.3V.
NB: Supply voltage for input and output buffers. All IO is single ended LVCMOS. No individual VREFs are needed.
LVDS Differential I/O Standard requires VIO = 2.5V Bank 3 is the only on with non-emulated LVDS
ESTIM
OPTOSTIM
NB: VCoax must NOT exceed 5.5V
TETHERED IO
NB: Inductors pass 250mA DC max before they are used to generate a flyback voltage. Because we are dealing with a very low current application, we can probably get away with inductors that saturate below 250 mA so long as they are capable of handling the current. The MLZ2012M100WT000 saturates at 2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
POWER
9DOF TRACKING
FPGA
SERIALIZER
WIRELESS IO
LOGGER
EXPANSION & TESTPOINTS
NB: Lockout @ 2.3V, which is min. programmable of MAX17048
NB: Worst case current consumption is ~80 mA for 4 chips.
I2C Selected
NB To get the best performance out of BNO055, it is recommended to use the external 32.768 kHz crystal.
South-East
East
South-West
West
North-West
North
North-East
Analog Ref - Internal VREF = 3.3V
Load will never be small enough that ECO matters and forcing PWM gives better ripple.
Programming interface
NB: 0.1 is not needed.
NB: Ths BLM has higher current rating than the others!
EPHYS
NB: I2C Addresses - 0x6C: write to MAX17048 - 0x6D: read from MAX17048 - 0x28: BNO055
NB: Switching residue filter.
NB: CLK2 drives PLL1
NB: GND for ease of routing.
MMCX
SMA
DAUGHER BOARDS

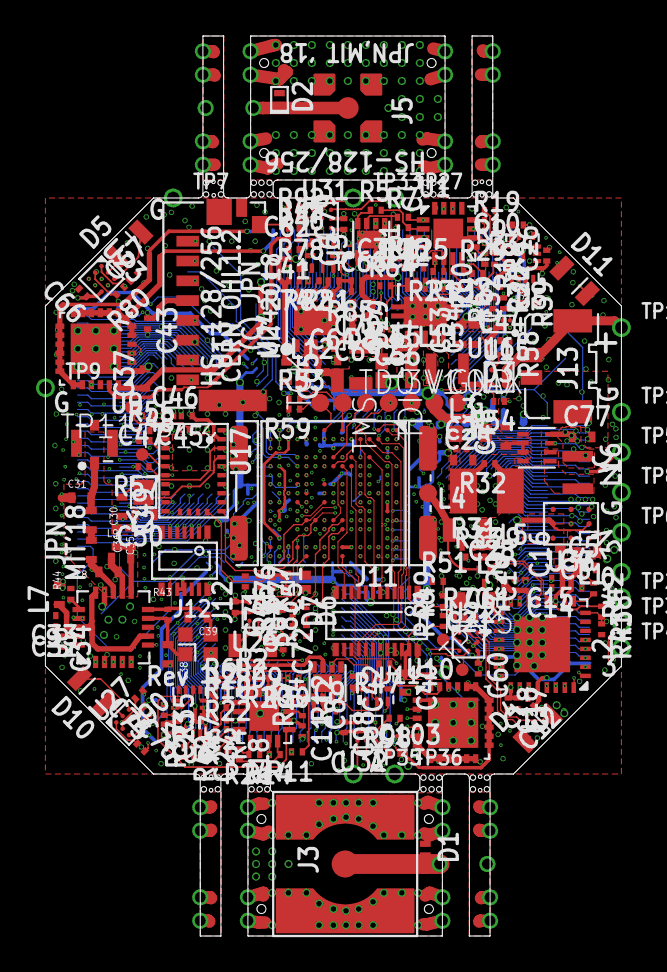
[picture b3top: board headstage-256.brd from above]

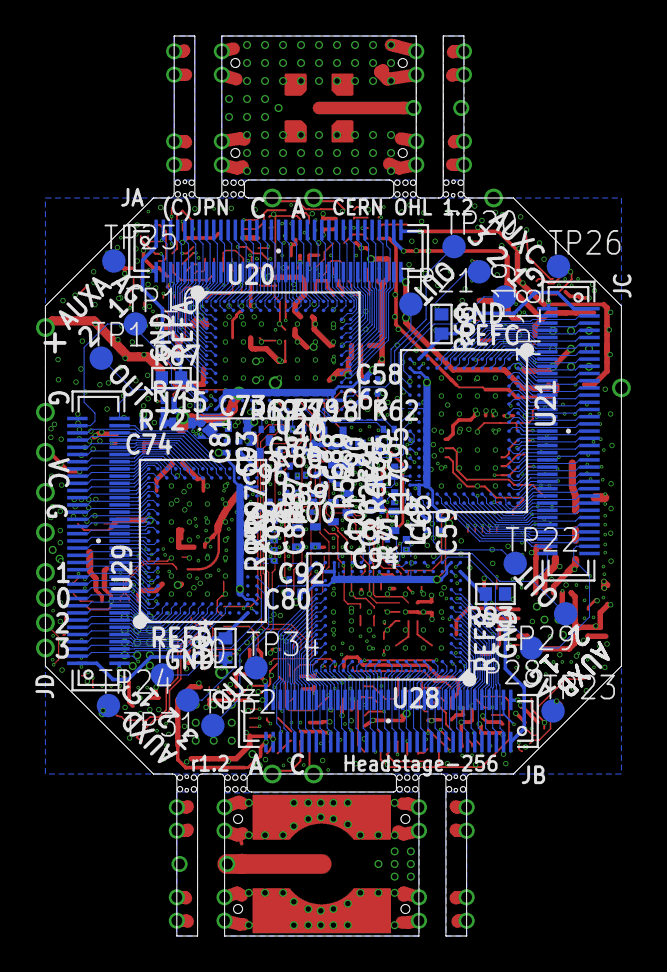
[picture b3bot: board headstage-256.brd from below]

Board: 8 copper layers, 32.0 x 50.0 mm, 326 parts (80 on the bottom side), 519 nets.

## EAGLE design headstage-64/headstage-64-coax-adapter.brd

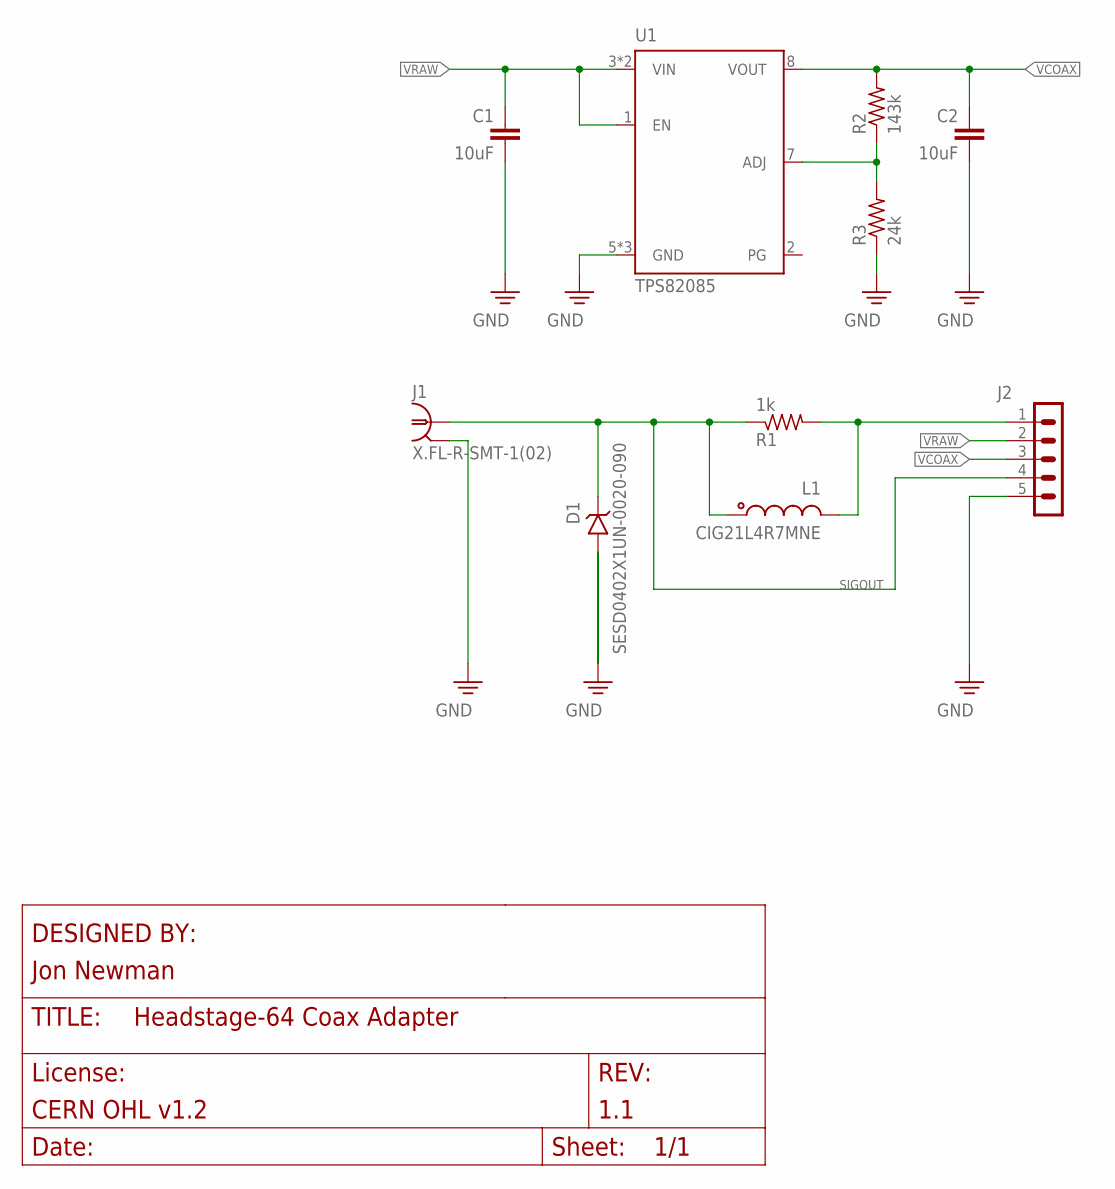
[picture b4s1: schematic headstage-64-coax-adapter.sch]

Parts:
C1, C2: 10uF; 0402T; PARTNO CL05A475MO5NUNC
D1: SESD0402X1UN-0020-090; 0402T-DFN
J1: X.FL-R-SMT-1(02); X_FL_R_SMT_1(02)
J2: PINHD-1X5_HEADSTAGE-64-REV1.4-DAUGHTER-CARD-CASTE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; HEADSTAGE-64-REV1.4-DAUGHTER-CARD-CASTELLATED
L1: CIG21L4R7MNE; 0805T
R1: 1k; 0201T
R2: 143k; 0201T
R3: 24k; 0201T
U1: TPS82085; MICROSIP9-2.8X3

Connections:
GND: C1.2, C2.2, D1.A, J1.P$2 (2), J1.P$3 (2), J1.P$4 (2), J2.5, R3.1, U1.5 (GND), U1.6 (GND), U1.PAD (GND)
unnamed: R2.1, R3.2, U1.7 (ADJ)
unnamed: J2.1, L1.2, R1.2
SIGOUT: D1.C, J1.P$1 (1), J2.4, L1.1, R1.1
VCOAX: C2.1, J2.3, R2.2, U1.8 (VOUT)
VRAW: C1.1, J2.2, U1.1 (EN), U1.3 (VIN), U1.4 (VIN)
